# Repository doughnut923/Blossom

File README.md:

# Blossom

An open-sourced Alice/Arisu style keyboard case. Modified from [FateNozomi's Arisu](https://github.com/FateNozomi/arisu-case)

## Features
- Designed for 3d printing
- Gasket Mounted Desgin using gasket strips on the side of the plate
   - Strip material: Poron Foam or Silicon Rubber
- Includes dxf files of sound dampening material between PCB and plate
- Compatible with [FateNozomi's PCB](https://github.com/FateNozomi/arisu-pcb)

## Layers

## Layout 

## Specifications 

- Dimensions: 30x142x375mm (DxHxW)
- Front Height: 16.5mm
- 5 degree typing angle

## About  the Repository
If you just want to build your own Blossom using the easiest steps just skip to [DIY Guide](#diy-guide)
Below is the contents of the respected folders in this GitHub Repo:
- `PCB files` - contains the Kicad project of the experimental version of the PCB(with underglow), modified from original FateNozomi's one.
- `Renders` - contains image assets.
- `blender` - contain Blender file of the case in case you need to do some edits to the model.
- ` case_stls` - stl files exported from Blender.
- `plate_dxfs` - contains dxf files for plate and gasket
- `production` - contains files necessary for DIY or production
- `qmk` - Modified keyboard firmware from arisu with added RGB underglow functionality.

# Notes
- **Use the files at your own risk**
- **PCB files are still under development,you can use it, but also at your own risk**

# DIY Guide
#### Things you need: 
| Item  | Image  | Description  | Related Files  | Place to Buy |
| ------------ | ------------ | ------------ | ------------ | ------------ |
| Upper Case * 1  |   | Upper section of the case  | [U_Case.stl](https://github.com/DoughnutTheGuy/Blossom/blob/main/production/case/U_Case.stl)  |  [PCBWay](https://www.pcbway.com/rapid-prototyping/manufacture/?type=2&reffercode=TOP) |
| Lower Case * 1  |   |  Lower Section of the case | [B_Case.stl](https://github.com/DoughnutTheGuy/Blossom/blob/main/production/case/B_Case.stl)  |  [PCBWay](https://www.pcbway.com/rapid-prototyping/manufacture/?type=2&reffercode=TOP) |
|  PCB * 1  |   | Can be chosed from experimental version, which have backlight. Or original FateNozomi's version.  | Original: [gerber](https://github.com/DoughnutTheGuy/Blossom/blob/main/production/pcb/original/arisu-pcb-v1.1-gerber.zip) [bom](https://github.com/DoughnutTheGuy/Blossom/blob/main/production/pcb/original/arisu_bom.csv)  [CPL](https://github.com/DoughnutTheGuy/Blossom/blob/main/production/pcb/original/arisu-all-pos.csv)  Experimental: [gerber](https://github.com/DoughnutTheGuy/Blossom/blob/main/production/pcb/experimental/blossom-pcb.gerber.zip) [BOM](https://github.com/DoughnutTheGuy/Blossom/blob/main/production/pcb/experimental/arisu_bom.csv) [CPL](https://github.com/DoughnutTheGuy/Blossom/blob/main/production/pcb/experimental/arisu-all-pos.csv)| [JLPCB](https://jlcpcb.com) [PCBWay](https://www.pcbway.com) |
| Gasket & Sound Dampening Foam * 1  |   | Can be Poron or Silicon  | [gasket_n_sdl.dxf](https://github.com/DoughnutTheGuy/Blossom/blob/main/production/gasket/gasket_n_sdl.dxf)  | [TaoBao](https://item.taobao.com/item.htm?spm=a230r.1.14.38.46936e836dHYfA&id=637356500647&ns=1&abbucket=9#detail)  |
| Plate * 1 |   | /  |  [plate.dxf](https://github.com/DoughnutTheGuy/Blossom/blob/main/production/plate/plate.dxf) |  [Ponoko](https://www.ponoko.com/materials)  [TaoBao(PC)](https://item.taobao.com/item.htm?spm=a312a.7700824.w4004-18046735553.2.28ff1436zVjIGW&id=565729881968) [SendCutSend](https://sendcutsend.com/)|
| M2.5 Screws * 8 | /  | /  |  / | [Ebay](https://www.ebay.com/sch/i.html?_from=R40&_trksid=p2380057.m570.l1313&_nkw=m2.5+*+4+hex+screws&_sacat=0) [Taobao](https://detail.tmall.com/item.htm?id=18868040917&spm=a1z0k.7385993.0.0.58e537decwL3jP&skuId=4328080057495) |
| M2.5 Insert * 8 | /  | /  |  / |  [Amazon](https://www.amazon.com/Knurled-Threaded-Embedment-Assortment-M2-533-5%EF%BC%88100pcs%EF%BC%89/dp/B07SPWZT5G?th=1) [Taobao](https://detail.tmall.com/item.htm?id=19528296472&spm=a1z0k.7385993.0.0.58e537decwL3jP) |

##### Other things you should probably have : Soldering Iron,  screw driver, switches, Hot Glue(Optional)

### Assembly
------------
**Step 1** - Install the switches into the plate

**Step 2** - place the sound dampening material between the plate and PCB

**Step 3** - Solder the switches

**Step 4** - Stick the gasket of the material of your choice to the extended positions on the plate

**Step 5**  - Install the M2.5 inserts in the 8 positions on the upper case shown below

**Step 6** - Place the plate with the pcb on top of the bottom case

**Step 7** - Cover it with the upper case

**Step 8** - Install screw in the following positions to fix both upper and bottom case

**Final Step** - Connect your keyboard to a computer. Download the [Arisu Firmware from VIA](https://caniusevia.com/docs/download_firmware/#0) and fiash it to your keyboard. Tools such as [QMK Toolbox](https://github.com/qmk/qmk_toolbox) Is recommended. Here is a [quick guide](https://www.youtube.com/watch?v=fuBJbdCFF0Q&t=203s) on how to use QMK toolbox just for reference.

If you are using the experimental version. you need to change the `config.h` file's `RGB_DI_PIN`'s value to `F4`

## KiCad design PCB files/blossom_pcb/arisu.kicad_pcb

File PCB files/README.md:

This PCB is uder developnment

Only have support for underglow

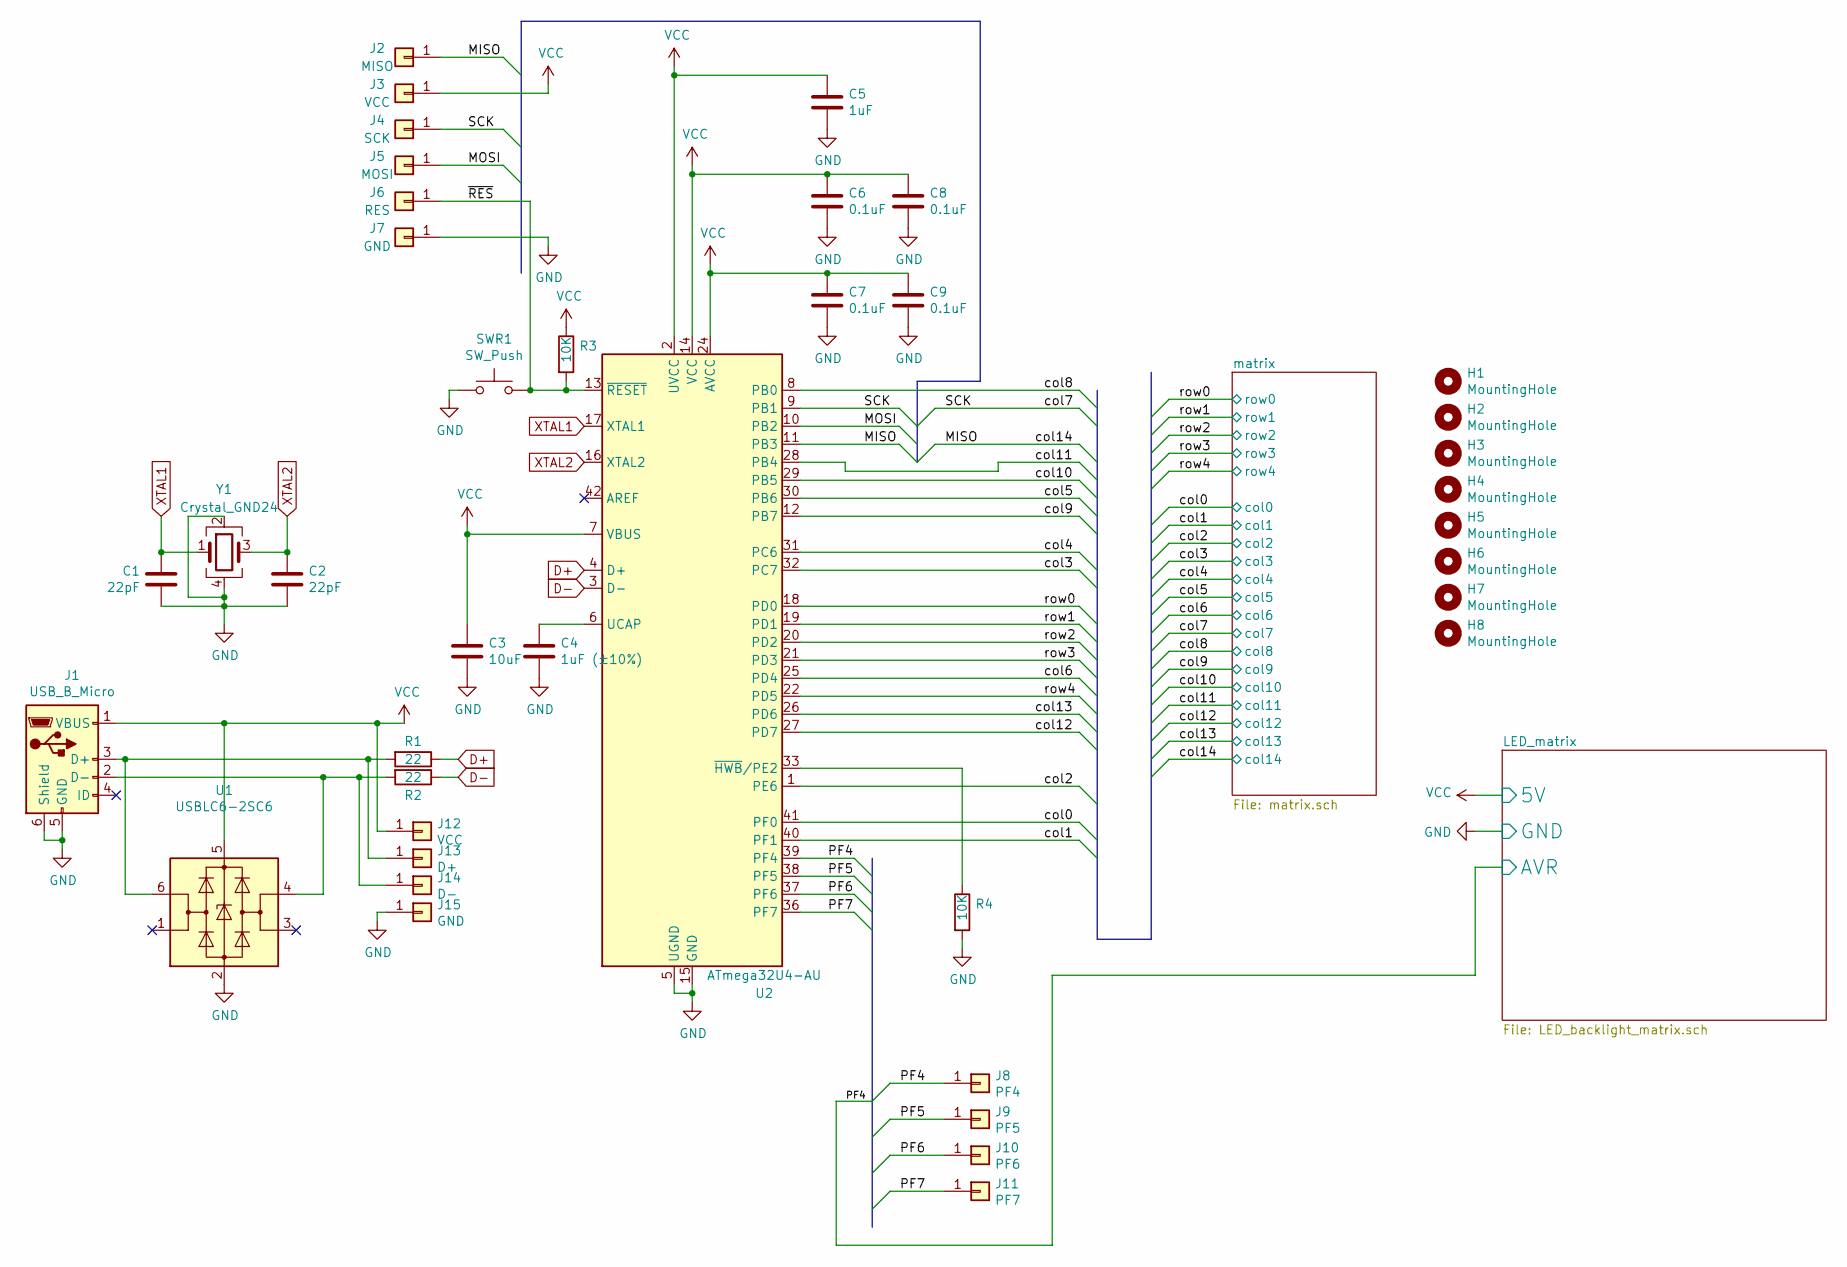
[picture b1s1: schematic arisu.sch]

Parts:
C1, C2: 22pF; C_0805_2012Metric
C3: 10uF; C_0805_2012Metric
C4: 1uF (±10%); C_0805_2012Metric
C5: 1uF; C_0805_2012Metric
C6, C7, C8, C9: 0.1uF; C_0805_2012Metric
H1, H2, H3, H4, H5, H6, H7, H8: MountingHole; MountingHole_2.2mm_M2_Pad
J1: USB_B_Micro; USB_Micro-B_Molex-105017-0001
J2: MISO; Pin_Header_Straight_1x01_Pitch2.54mm
J3, J12: VCC; Pin_Header_Straight_1x01_Pitch2.54mm
J4: SCK; Pin_Header_Straight_1x01_Pitch2.54mm
J5: MOSI; Pin_Header_Straight_1x01_Pitch2.54mm
J6: RES; Pin_Header_Straight_1x01_Pitch2.54mm
J7, J15: GND; Pin_Header_Straight_1x01_Pitch2.54mm
J8: PF4; Pin_Header_Straight_1x01_Pitch2.54mm
J9: PF5; Pin_Header_Straight_1x01_Pitch2.54mm
J10: PF6; Pin_Header_Straight_1x01_Pitch2.54mm
J11: PF7; Pin_Header_Straight_1x01_Pitch2.54mm
J13: D+; Pin_Header_Straight_1x01_Pitch2.54mm
J14: D-; Pin_Header_Straight_1x01_Pitch2.54mm
R1, R2: 22; R_0805_2012Metric
R3, R4: 10K; R_0805_2012Metric
SWR1: SW_Push; SW_SPST_TL3342
U1: USBLC6-2SC6; SOT-23-6_Handsoldering
U2: ATmega32U4-AU; TQFP-44_10x10mm_Pitch0.8mm
Y1: Crystal_GND24; Crystal_SMD_3225-4Pin_3.2x2.5mm

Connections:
/MISO: J2.1, U2.11 (PB3); also elsewhere on the board
/MOSI: J5.1, U2.10 (PB2)
/PF4: J8.1, U2.39 (PF4); also elsewhere on the board
/PF5: J9.1, U2.38 (PF5)
/PF6: J10.1, U2.37 (PF6)
/PF7: J11.1, U2.36 (PF7)
/SCK: J4.1, U2.9 (PB1); also elsewhere on the board
/col0: U2.41 (PF0); also elsewhere on the board
/col1: U2.40 (PF1); also elsewhere on the board
/col2: U2.1 (PE6); also elsewhere on the board
/col3: U2.32 (PC7); also elsewhere on the board
/col4: U2.31 (PC6); also elsewhere on the board
/col5: U2.30 (PB6); also elsewhere on the board
/col6: U2.25 (PD4); also elsewhere on the board
/col8: U2.8 (PB0); also elsewhere on the board
/col9: U2.12 (PB7); also elsewhere on the board
/col10: U2.29 (PB5); also elsewhere on the board
/col11: U2.28 (PB4); also elsewhere on the board
/col12: U2.27 (PD7); also elsewhere on the board
/col13: U2.26 (PD6); also elsewhere on the board
/row0: U2.18 (PD0); also elsewhere on the board
/row1: U2.19 (PD1); also elsewhere on the board
/row2: U2.20 (PD2); also elsewhere on the board
/row3: U2.21 (PD3); also elsewhere on the board
/row4: U2.22 (PD5); also elsewhere on the board
/~RES~: J6.1, R3.2, SWR1.2, U2.13 (~RESET)
D+: R1.1, U2.4 (D+)
D-: R2.1, U2.3 (D-)
GND: C1.1, C2.2, C3.2, C4.2, C5.2, C6.2, C7.2, C8.2, C9.2, J1.5 (GND), J1.6 (Shield), J7.1, J15.1, R4.2, SWR1.1, U1.2 (GND), U2.5 (UGND), U2.15 (GND), U2.23 (GND), U2.35 (GND), U2.43 (GND), Y1.2, Y1.4; also elsewhere on the board
unnamed: C4.1, U2.6 (UCAP)
unnamed: J1.2 (D-), J14.1, R2.2, U1.4 (I/O2)
unnamed: J1.3 (D+), J13.1, R1.2, U1.6 (I/O1)
unnamed: R4.1, U2.33 (~HWB~/PE2)
VCC: C3.1, C5.1, C6.1, C7.1, C8.1, C9.1, J1.1 (VBUS), J3.1, J12.1, R3.1, U1.5 (VBUS), U2.2 (UVCC), U2.7 (VBUS), U2.14 (VCC), U2.24 (AVCC), U2.34 (VCC), U2.44 (AVCC); also elsewhere on the board
XTAL1: C1.2, U2.17 (XTAL1), Y1.1
XTAL2: C2.1, U2.16 (XTAL2), Y1.3

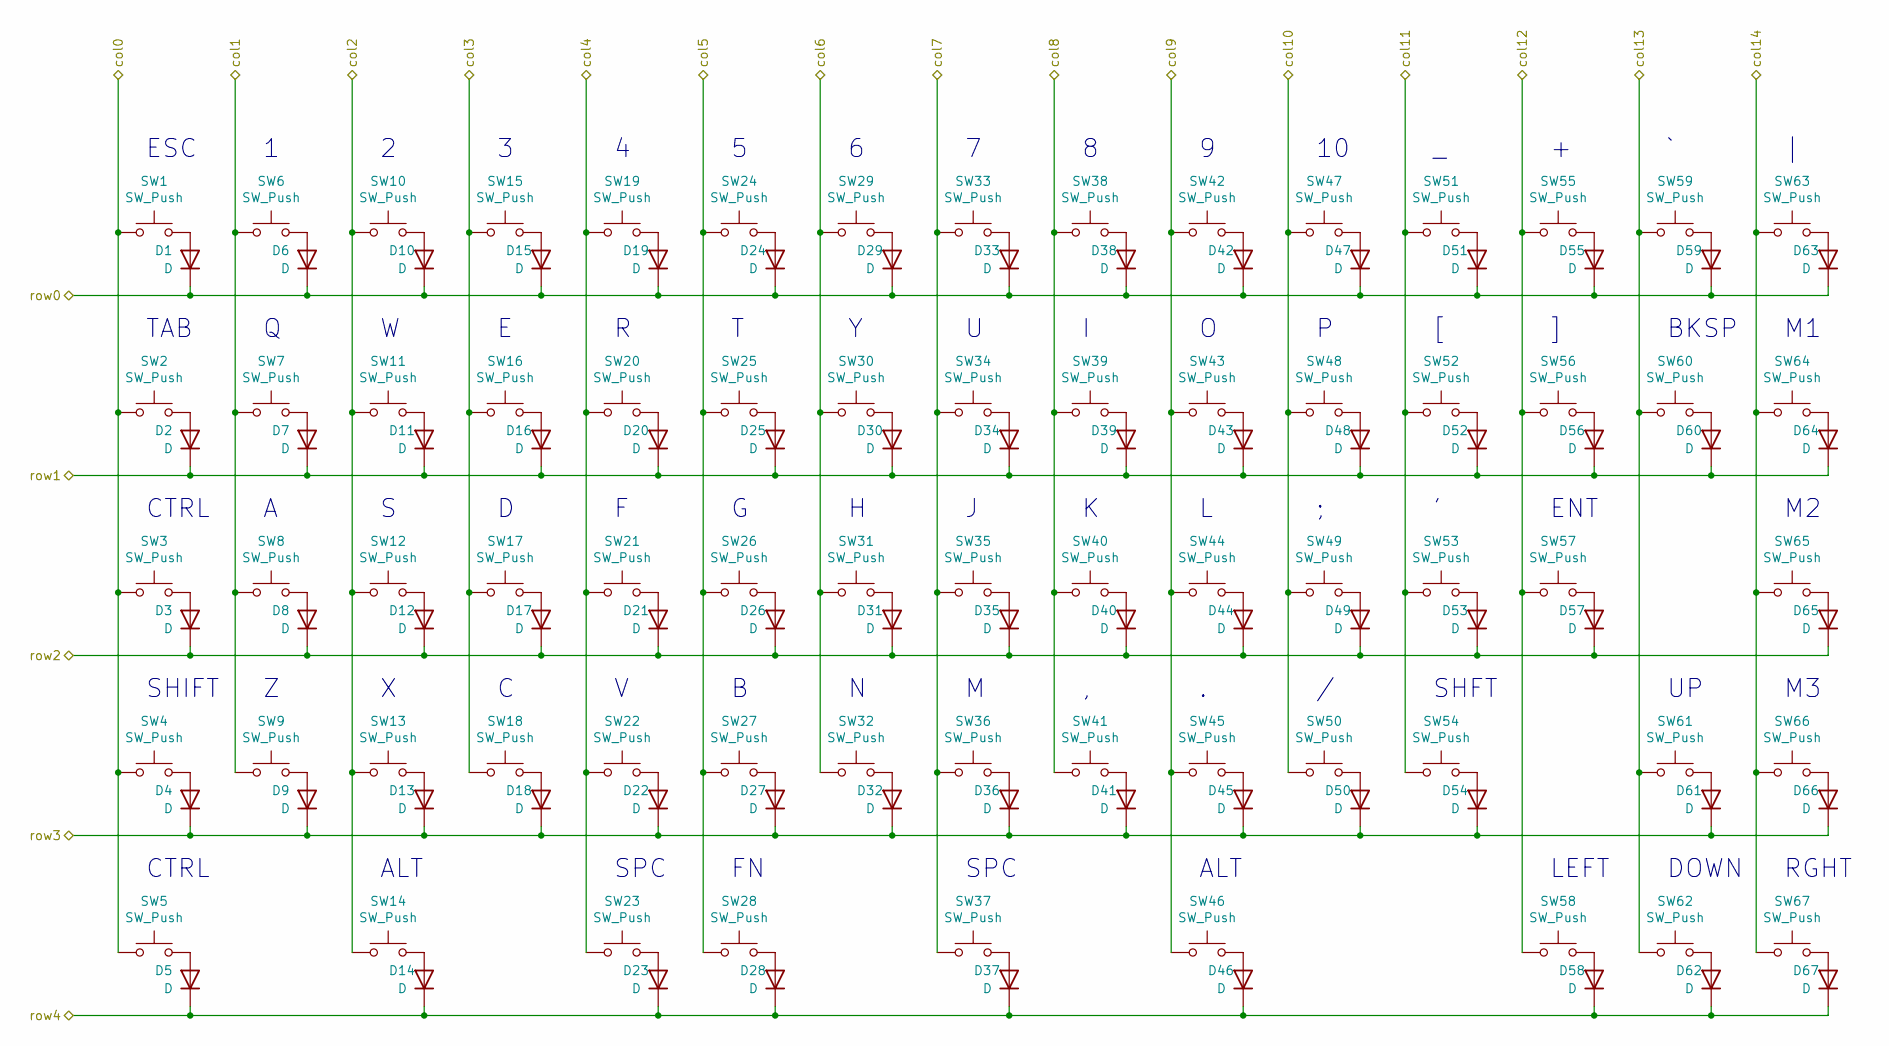
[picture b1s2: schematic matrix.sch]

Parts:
D1, D2, D3, D4, D5, D6, D7, D8, D9, D10, D11, D12, D13, D14, D15, D16, D17, D18, D19, D20, D21, D22, D23, D24, D25, D26, D27, D28, D29, D30, D31, D32, D33, D34, D35, D36, D37, D38, D39, D40, D41, D42, D43, D44, D45, D46, D47, D48, D49, D50, D51, D52, D53, D54, D55, D56, D57, D58, D59, D60, D61, D62, D63, D64, D65, D66, D67: D; D_SOD-123
SW1, SW6, SW7, SW8, SW9, SW10, SW11, SW12, SW13, SW15, SW16, SW17, SW18, SW19, SW20, SW21, SW22, SW24, SW25, SW26, SW27, SW28, SW29, SW30, SW31, SW32, SW33, SW34, SW35, SW36, SW38, SW39, SW40, SW41, SW42, SW43, SW44, SW45, SW47, SW48, SW49, SW50, SW51, SW52, SW53, SW55, SW56, SW58, SW59, SW61, SW62, SW63, SW64, SW65, SW66, SW67: SW_Push; SW_Cherry_MX_1.00u_PCB
SW2, SW5, SW14, SW46, SW60: SW_Push; SW_Cherry_MX_1.50u_PCB
SW3, SW54: SW_Push; SW_Cherry_MX_1.75u_PCB
SW4: SW_Push; SW_Cherry_MX_2.25u_PCB
SW23: SW_Push; SW_Cherry_MX_2.00u_PCB_ReversedStabilizers
SW37: SW_Push; SW_Cherry_MX_2.75u_PCB_ReversedStabilizers
SW57: SW_Push; SW_Cherry_MX_2.25u_PCB_ReversedStabilizers

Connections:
/MISO: SW63.1, SW64.1, SW65.1, SW66.1, SW67.1; also elsewhere on the board
/SCK: SW33.1, SW34.1, SW35.1, SW36.1, SW37.1; also elsewhere on the board
/col0: SW1.1, SW2.1, SW3.1, SW4.1, SW5.1; also elsewhere on the board
/col1: SW6.1, SW7.1, SW8.1, SW9.1; also elsewhere on the board
/col2: SW10.1, SW11.1, SW12.1, SW13.1, SW14.1; also elsewhere on the board
/col3: SW15.1, SW16.1, SW17.1, SW18.1; also elsewhere on the board
/col4: SW19.1, SW20.1, SW21.1, SW22.1, SW23.1; also elsewhere on the board
/col5: SW24.1, SW25.1, SW26.1, SW27.1, SW28.1; also elsewhere on the board
/col6: SW29.1, SW30.1, SW31.1, SW32.1; also elsewhere on the board
/col8: SW38.1, SW39.1, SW40.1, SW41.1; also elsewhere on the board
/col9: SW42.1, SW43.1, SW44.1, SW45.1, SW46.1; also elsewhere on the board
/col10: SW47.1, SW48.1, SW49.1, SW50.1; also elsewhere on the board
/col11: SW51.1, SW52.1, SW53.1, SW54.1; also elsewhere on the board
/col12: SW55.1, SW56.1, SW57.1, SW58.1; also elsewhere on the board
/col13: SW59.1, SW60.1, SW61.1, SW62.1; also elsewhere on the board
/row0: D1.1 (K), D6.1 (K), D10.1 (K), D15.1 (K), D19.1 (K), D24.1 (K), D29.1 (K), D33.1 (K), D38.1 (K), D42.1 (K), D47.1 (K), D51.1 (K), D55.1 (K), D59.1 (K), D63.1 (K); also elsewhere on the board
/row1: D2.1 (K), D7.1 (K), D11.1 (K), D16.1 (K), D20.1 (K), D25.1 (K), D30.1 (K), D34.1 (K), D39.1 (K), D43.1 (K), D48.1 (K), D52.1 (K), D56.1 (K), D60.1 (K), D64.1 (K); also elsewhere on the board
/row2: D3.1 (K), D8.1 (K), D12.1 (K), D17.1 (K), D21.1 (K), D26.1 (K), D31.1 (K), D35.1 (K), D40.1 (K), D44.1 (K), D49.1 (K), D53.1 (K), D57.1 (K), D65.1 (K); also elsewhere on the board
/row3: D4.1 (K), D9.1 (K), D13.1 (K), D18.1 (K), D22.1 (K), D27.1 (K), D32.1 (K), D36.1 (K), D41.1 (K), D45.1 (K), D50.1 (K), D54.1 (K), D61.1 (K), D66.1 (K); also elsewhere on the board
/row4: D5.1 (K), D14.1 (K), D23.1 (K), D28.1 (K), D37.1 (K), D46.1 (K), D58.1 (K), D62.1 (K), D67.1 (K); also elsewhere on the board
unnamed: D1.2 (A), SW1.2
unnamed: D2.2 (A), SW2.2
unnamed: D3.2 (A), SW3.2
unnamed: D4.2 (A), SW4.2
unnamed: D5.2 (A), SW5.2
unnamed: D6.2 (A), SW6.2
unnamed: D7.2 (A), SW7.2
unnamed: D8.2 (A), SW8.2
unnamed: D9.2 (A), SW9.2
unnamed: D10.2 (A), SW10.2
unnamed: D11.2 (A), SW11.2
unnamed: D12.2 (A), SW12.2
unnamed: D13.2 (A), SW13.2
unnamed: D14.2 (A), SW14.2
unnamed: D15.2 (A), SW15.2
unnamed: D16.2 (A), SW16.2
unnamed: D17.2 (A), SW17.2
unnamed: D18.2 (A), SW18.2
unnamed: D19.2 (A), SW19.2
unnamed: D20.2 (A), SW20.2
unnamed: D21.2 (A), SW21.2
unnamed: D22.2 (A), SW22.2
unnamed: D23.2 (A), SW23.2
unnamed: D24.2 (A), SW24.2
unnamed: D25.2 (A), SW25.2
unnamed: D26.2 (A), SW26.2
unnamed: D27.2 (A), SW27.2
unnamed: D28.2 (A), SW28.2
unnamed: D29.2 (A), SW29.2
unnamed: D30.2 (A), SW30.2
unnamed: D31.2 (A), SW31.2
unnamed: D32.2 (A), SW32.2
unnamed: D33.2 (A), SW33.2
unnamed: D34.2 (A), SW34.2
unnamed: D35.2 (A), SW35.2
unnamed: D36.2 (A), SW36.2
unnamed: D37.2 (A), SW37.2
unnamed: D38.2 (A), SW38.2
unnamed: D39.2 (A), SW39.2
unnamed: D40.2 (A), SW40.2
unnamed: D41.2 (A), SW41.2
unnamed: D42.2 (A), SW42.2
unnamed: D43.2 (A), SW43.2
unnamed: D44.2 (A), SW44.2
unnamed: D45.2 (A), SW45.2
unnamed: D46.2 (A), SW46.2
unnamed: D47.2 (A), SW47.2
unnamed: D48.2 (A), SW48.2
unnamed: D49.2 (A), SW49.2
unnamed: D50.2 (A), SW50.2
unnamed: D51.2 (A), SW51.2
unnamed: D52.2 (A), SW52.2
unnamed: D53.2 (A), SW53.2
unnamed: D54.2 (A), SW54.2
unnamed: D55.2 (A), SW55.2
unnamed: D56.2 (A), SW56.2
unnamed: D57.2 (A), SW57.2
unnamed: D58.2 (A), SW58.2
unnamed: D59.2 (A), SW59.2
unnamed: D60.2 (A), SW60.2
unnamed: D61.2 (A), SW61.2
unnamed: D62.2 (A), SW62.2
unnamed: D63.2 (A), SW63.2
unnamed: D64.2 (A), SW64.2
unnamed: D65.2 (A), SW65.2
unnamed: D66.2 (A), SW66.2
unnamed: D67.2 (A), SW67.2

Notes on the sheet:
ESC
TAB
BKSP
CTRL
ENT
SHIFT
SHFT
ALT
SPC
DOWN
LEFT
RGHT

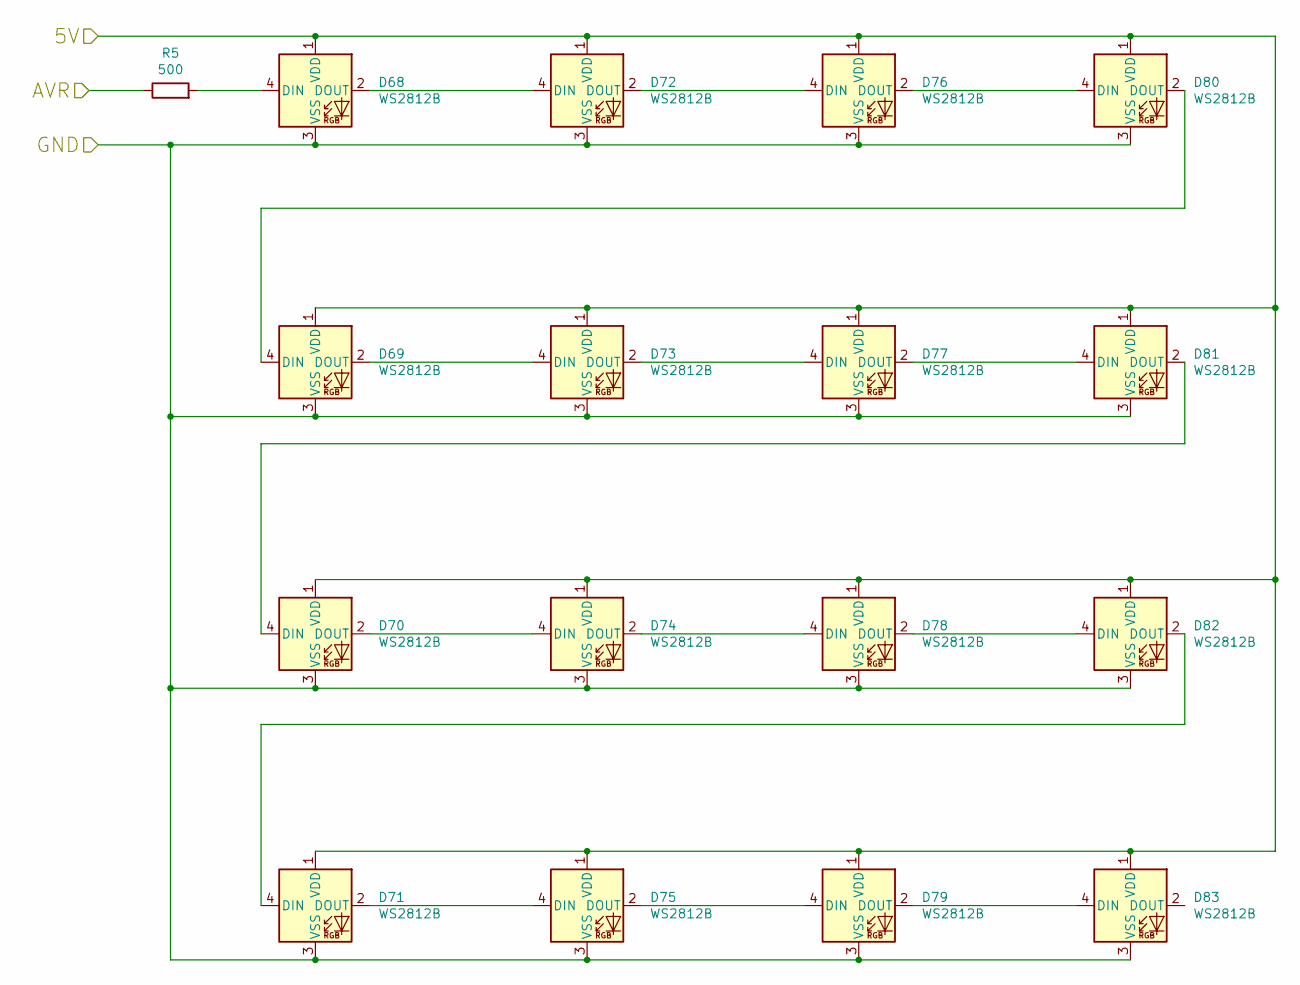
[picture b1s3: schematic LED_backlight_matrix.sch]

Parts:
D68, D69, D70, D71, D72, D73, D74, D75, D76, D77, D78, D79, D80, D81, D82, D83: WS2812B; LED_WS2812B_PLCC4_5.0x5.0mm_P3.2mm
R5: 500; R_0805_2012Metric

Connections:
/PF4: R5.1; also elsewhere on the board
GND: D68.3 (VSS), D69.3 (VSS), D70.3 (VSS), D71.3 (VSS), D72.3 (VSS), D73.3 (VSS), D74.3 (VSS), D75.3 (VSS), D76.3 (VSS), D77.3 (VSS), D78.3 (VSS), D79.3 (VSS), D80.3 (VSS), D81.3 (VSS), D82.3 (VSS), D83.3 (VSS); also elsewhere on the board
unnamed: D68.2 (DOUT), D72.4 (DIN)
unnamed: D68.4 (DIN), R5.2
unnamed: D69.2 (DOUT), D73.4 (DIN)
unnamed: D69.4 (DIN), D80.2 (DOUT)
unnamed: D70.2 (DOUT), D74.4 (DIN)
unnamed: D70.4 (DIN), D81.2 (DOUT)
unnamed: D71.2 (DOUT), D75.4 (DIN)
unnamed: D71.4 (DIN), D82.2 (DOUT)
unnamed: D72.2 (DOUT), D76.4 (DIN)
unnamed: D73.2 (DOUT), D77.4 (DIN)
unnamed: D74.2 (DOUT), D78.4 (DIN)
unnamed: D75.2 (DOUT), D79.4 (DIN)
unnamed: D76.2 (DOUT), D80.4 (DIN)
unnamed: D77.2 (DOUT), D81.4 (DIN)
unnamed: D78.2 (DOUT), D82.4 (DIN)
unnamed: D79.2 (DOUT), D83.4 (DIN)
VCC: D68.1 (VDD), D69.1 (VDD), D70.1 (VDD), D71.1 (VDD), D72.1 (VDD), D73.1 (VDD), D74.1 (VDD), D75.1 (VDD), D76.1 (VDD), D77.1 (VDD), D78.1 (VDD), D79.1 (VDD), D80.1 (VDD), D81.1 (VDD), D82.1 (VDD), D83.1 (VDD); also elsewhere on the board

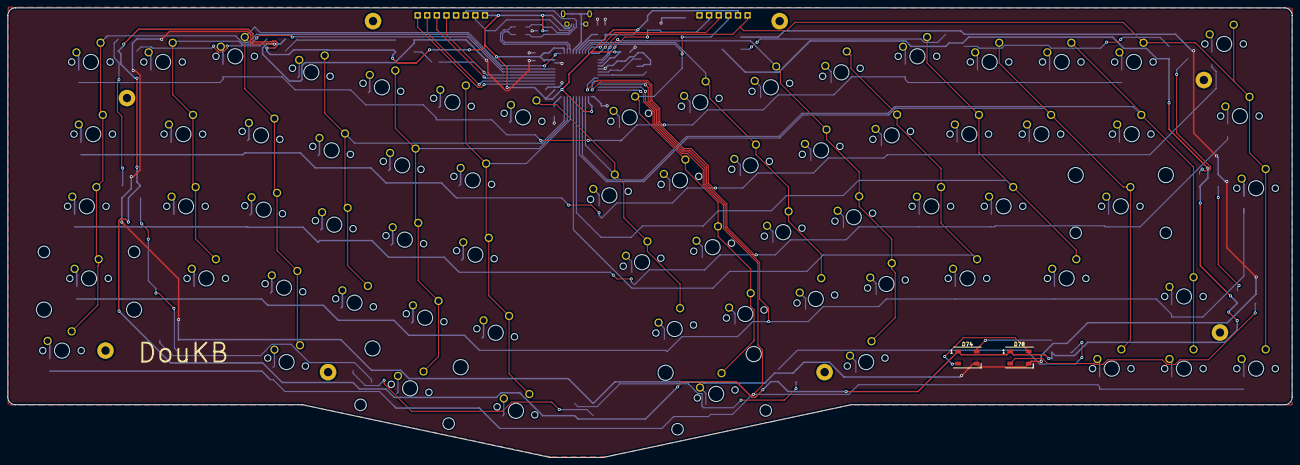
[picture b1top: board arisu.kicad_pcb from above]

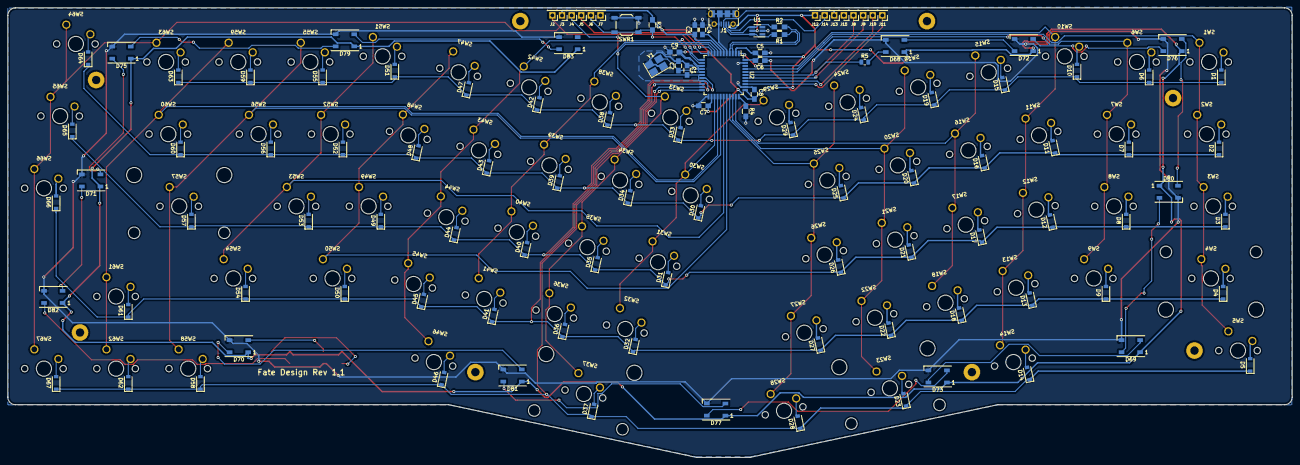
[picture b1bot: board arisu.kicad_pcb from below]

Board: 2 copper layers, 339.1 x 118.7 mm, 191 parts (114 on the bottom side), 119 nets.

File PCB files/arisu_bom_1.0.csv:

Component,Description,Part,References,Value,Footprint,Quantity Per PCB,Datasheet
1,Unpolarized capacitor,C,C6 C7 C8 C9,0.1uF,C_0805_HandSoldering,4,~
2,Unpolarized capacitor,C,C3,10uF,C_0805_HandSoldering,1,~
3,Unpolarized capacitor,C,C5,1uF,C_0805_HandSoldering,1,~
4,Unpolarized capacitor,C,C4,1uF (±10%),C_0805_HandSoldering,1,~
5,Unpolarized capacitor,C,C1 C2,22pF,C_0805_HandSoldering,2,~
6,Diode,D,D1 D2 D3 D4 D5 D6 D7 D8 D9 D10 D11 D12 D13 D14 D15 D16 D17 D18 D19 D20 D21 D22 D23 D24 D25 D26 D27 D28 D29 D30 D31 D32 D33 D34 D35 D36 D37 D38 D39 D40 D41 D42 D43 D44 D45 D46 D47 D48 D49 D50 D51 D52 D53 D54 D55 D56 D57 D58 D59 D60 D61 D62 D63 D64 D65 D66 D67,D,D_SOD-123,67,~
7,"Generic connector, single row, 01x01, script generated (kicad-library-utils/schlib/autogen/connector/)",Conn_01x01,J13,D+,Pin_Header_Straight_1x01_Pitch2.54mm,1,~
8,"Generic connector, single row, 01x01, script generated (kicad-library-utils/schlib/autogen/connector/)",Conn_01x01,J14,D-,Pin_Header_Straight_1x01_Pitch2.54mm,1,~
9,"Generic connector, single row, 01x01, script generated (kicad-library-utils/schlib/autogen/connector/)",Conn_01x01,J7 J15,GND,Pin_Header_Straight_1x01_Pitch2.54mm,2,~
10,"Generic connector, single row, 01x01, script generated (kicad-library-utils/schlib/autogen/connector/)",Conn_01x01,J2,MISO,Pin_Header_Straight_1x01_Pitch2.54mm,1,~
11,"Generic connector, single row, 01x01, script generated (kicad-library-utils/schlib/autogen/connector/)",Conn_01x01,J5,MOSI,Pin_Header_Straight_1x01_Pitch2.54mm,1,~
12,"Generic connector, single row, 01x01, script generated (kicad-library-utils/schlib/autogen/connector/)",Conn_01x01,J8,PF4,Pin_Header_Straight_1x01_Pitch2.54mm,1,~
13,"Generic connector, single row, 01x01, script generated (kicad-library-utils/schlib/autogen/connector/)",Conn_01x01,J9,PF5,Pin_Header_Straight_1x01_Pitch2.54mm,1,~
14,"Generic connector, single row, 01x01, script generated (kicad-library-utils/schlib/autogen/connector/)",Conn_01x01,J10,PF6,Pin_Header_Straight_1x01_Pitch2.54mm,1,~
15,"Generic connector, single row, 01x01, script generated (kicad-library-utils/schlib/autogen/connector/)",Conn_01x01,J11,PF7,Pin_Header_Straight_1x01_Pitch2.54mm,1,~
16,"Generic connector, single row, 01x01, script generated (kicad-library-utils/schlib/autogen/connector/)",Conn_01x01,J6,RES,Pin_Header_Straight_1x01_Pitch2.54mm,1,~
17,"Generic connector, single row, 01x01, script generated (kicad-library-utils/schlib/autogen/connector/)",Conn_01x01,J4,SCK,Pin_Header_Straight_1x01_Pitch2.54mm,1,~
18,USB Micro Type B connector,USB_B_Micro,J1,USB_B_Micro,USB_Micro-B_Molex-105017-0001,1,~
19,"Generic connector, single row, 01x01, script generated (kicad-library-utils/schlib/autogen/connector/)",Conn_01x01,J3 J12,VCC,Pin_Header_Straight_1x01_Pitch2.54mm,2,~
20,Resistor,R,R3 R4,10K,R_0805_HandSoldering,2,~
21,Resistor,R,R1 R2,22,R_0805_HandSoldering,2,~
22,"Push button switch, generic, two pins",SW_Push,SW1 SW6 SW7 SW8 SW9 SW10 SW11 SW12 SW13 SW15 SW16 SW17 SW18 SW19 SW20 SW21 SW22 SW24 SW25 SW26 SW27 SW28 SW29 SW30 SW31 SW32 SW33 SW34 SW35 SW36 SW38 SW39 SW40 SW41 SW42 SW43 SW44 SW45 SW47 SW48 SW49 SW50 SW51 SW52 SW53 SW55 SW56 SW58 SW59 SW61 SW62 SW63 SW64 SW65 SW66 SW67,SW_Push,SW_Cherry_MX_1.00u_PCB,56,
23,"Push button switch, generic, two pins",SW_Push,SW2 SW5 SW14 SW46 SW60,SW_Push,SW_Cherry_MX_1.50u_PCB,5,
24,"Push button switch, generic, two pins",SW_Push,SW23,SW_Push,SW_Cherry_MX_2.00u_PCB_ReversedStabilizers,1,
25,"Push button switch, generic, two pins",SW_Push,SW3 SW54,SW_Push,SW_Cherry_MX_1.75u_PCB,2,
26,"Push button switch, generic, two pins",SW_Push,SW37,SW_Push,SW_Cherry_MX_2.75u_PCB_ReversedStabilizers,1,
27,"Push button switch, generic, two pins",SW_Push,SW4,SW_Push,SW_Cherry_MX_2.25u_PCB,1,
28,"Push button switch, generic, two pins",SW_Push,SW57,SW_Push,SW_Cherry_MX_2.25u_PCB_ReversedStabilizers,1,
29,"Push button switch, generic, two pins",SW_Push,SWR1,SW_Push,SW_SPST_TL3342,1,
30,"16MHz, 32kB Flash, 2.5kB SRAM, 1kB EEPROM, USB 2.0, TQFP-44",ATmega32U4-AU,U2,ATmega32U4-AU,TQFP-44_10x10mm_Pitch0.8mm,1,http://ww1.microchip.com/downloads/en/DeviceDoc/Atmel-7766-8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
31,"Bidirectional ESD Protection Diode, SOT-23-6",USBLC6-2SC6,U1,USBLC6-2SC6,SOT-23-6_Handsoldering,1,http://www2.st.com/resource/en/datasheet/CD00050750.pdf
32,"Four pin crystal, GND on pins 2 and 4",Crystal_GND24,Y1,Crystal_GND24,Crystal_SMD_SeikoEpson_FA238-4pin_3.2x2.5mm_HandSoldering,1,~





Component Groups:,32
Component Count:,166
Fitted Components:,166
Number of PCBs:,1
Total components:,166
Schematic Version:,1.0
Schematic Date:,
BoM Date:,2/10/2019 10:20:54 PM
Schematic Source:,D:\Users\Will\Documents\arisu-pcb\arisu.sch
KiCad Version:,Eeschema (5.0.2)-1

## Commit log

2021-08-06 Added stl pcb dxf render
2021-08-07 Done desgin rule check on pcb and removed outlying wiring
2021-08-07 Some adjustments
    Increase height for upper casing
2021-08-14 repaired non manifold things on upper case
2021-08-14 update blend
2021-08-14 Update Renders
2021-09-08 minor fix
2021-09-08 fix top and add bevel
2021-09-12 some updates
2021-09-30 update no hole case thing
2021-09-30 update to no gasket hole thing
2021-09-30 added case without logo
2021-09-30 add logo
2021-10-01 Added keyboard/arisu/ config.h rbg pin
2021-10-01 added arisu pcb
2021-10-02 added cost reduction holes
2021-10-02 new renders
2021-10-03 add proto images
2021-11-12 update production folder
2021-11-12 Changed names
2021-11-13 added new images
2021-11-13 update images
2021-11-13 add layout ref
2022-03-25 Minor changes on blend
